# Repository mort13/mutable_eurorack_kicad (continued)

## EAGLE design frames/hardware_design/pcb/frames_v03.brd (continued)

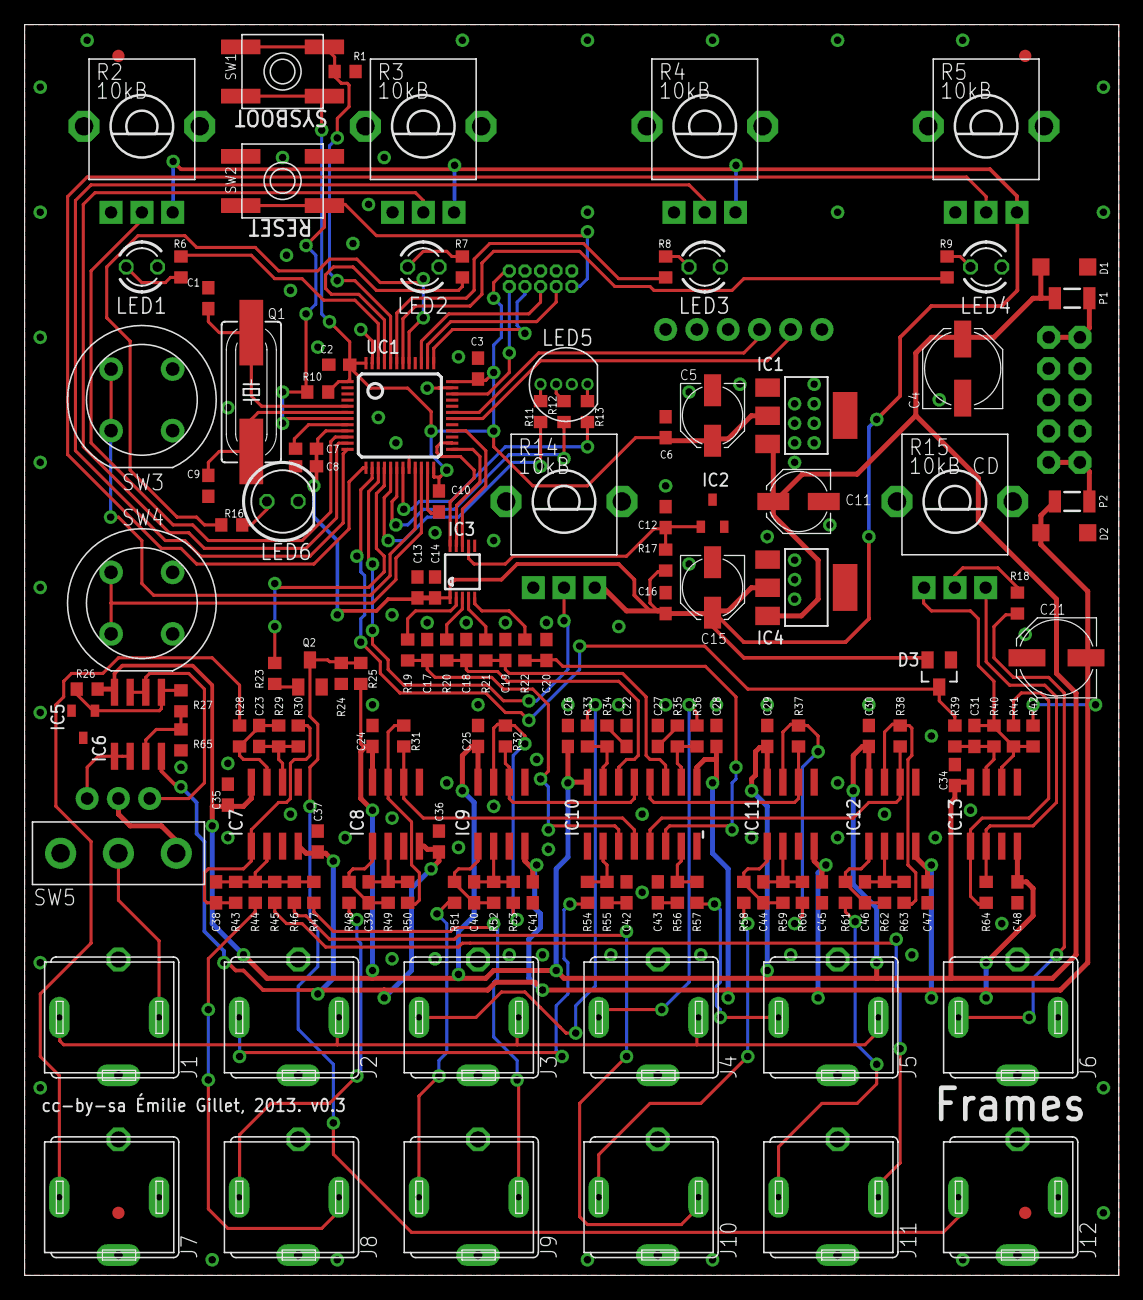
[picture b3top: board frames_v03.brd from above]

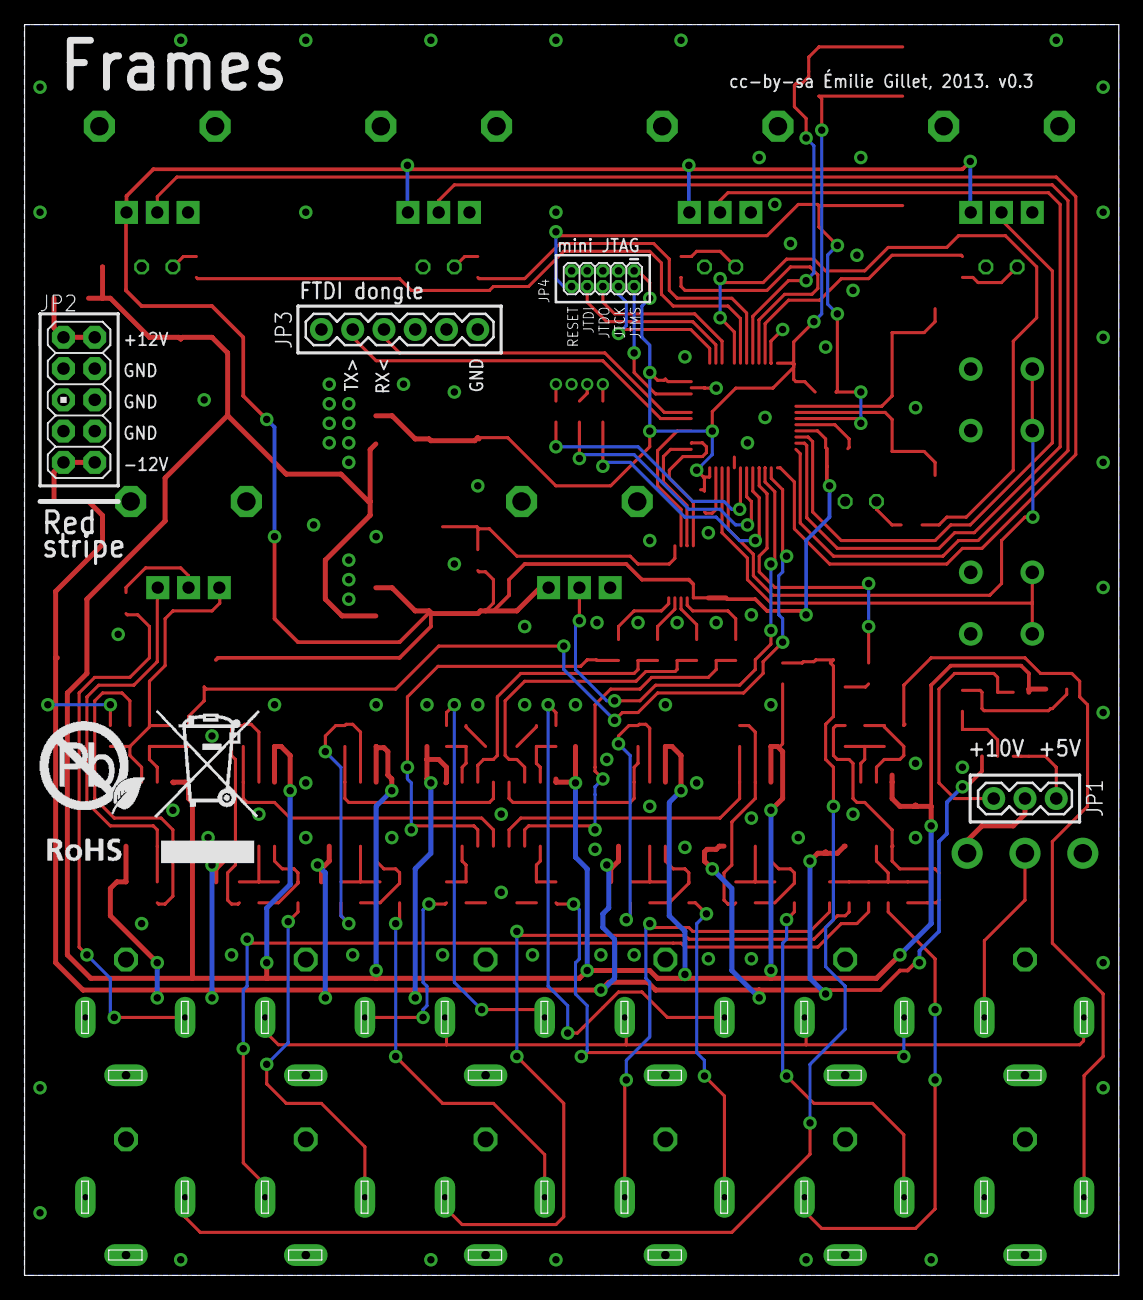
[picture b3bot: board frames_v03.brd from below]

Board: 2 copper layers, 88.9 x 101.6 mm, 165 parts (5 on the bottom side), 110 nets.

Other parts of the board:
U$1: EURORACK_TEMPLATE
U$3: ROHS_BIG

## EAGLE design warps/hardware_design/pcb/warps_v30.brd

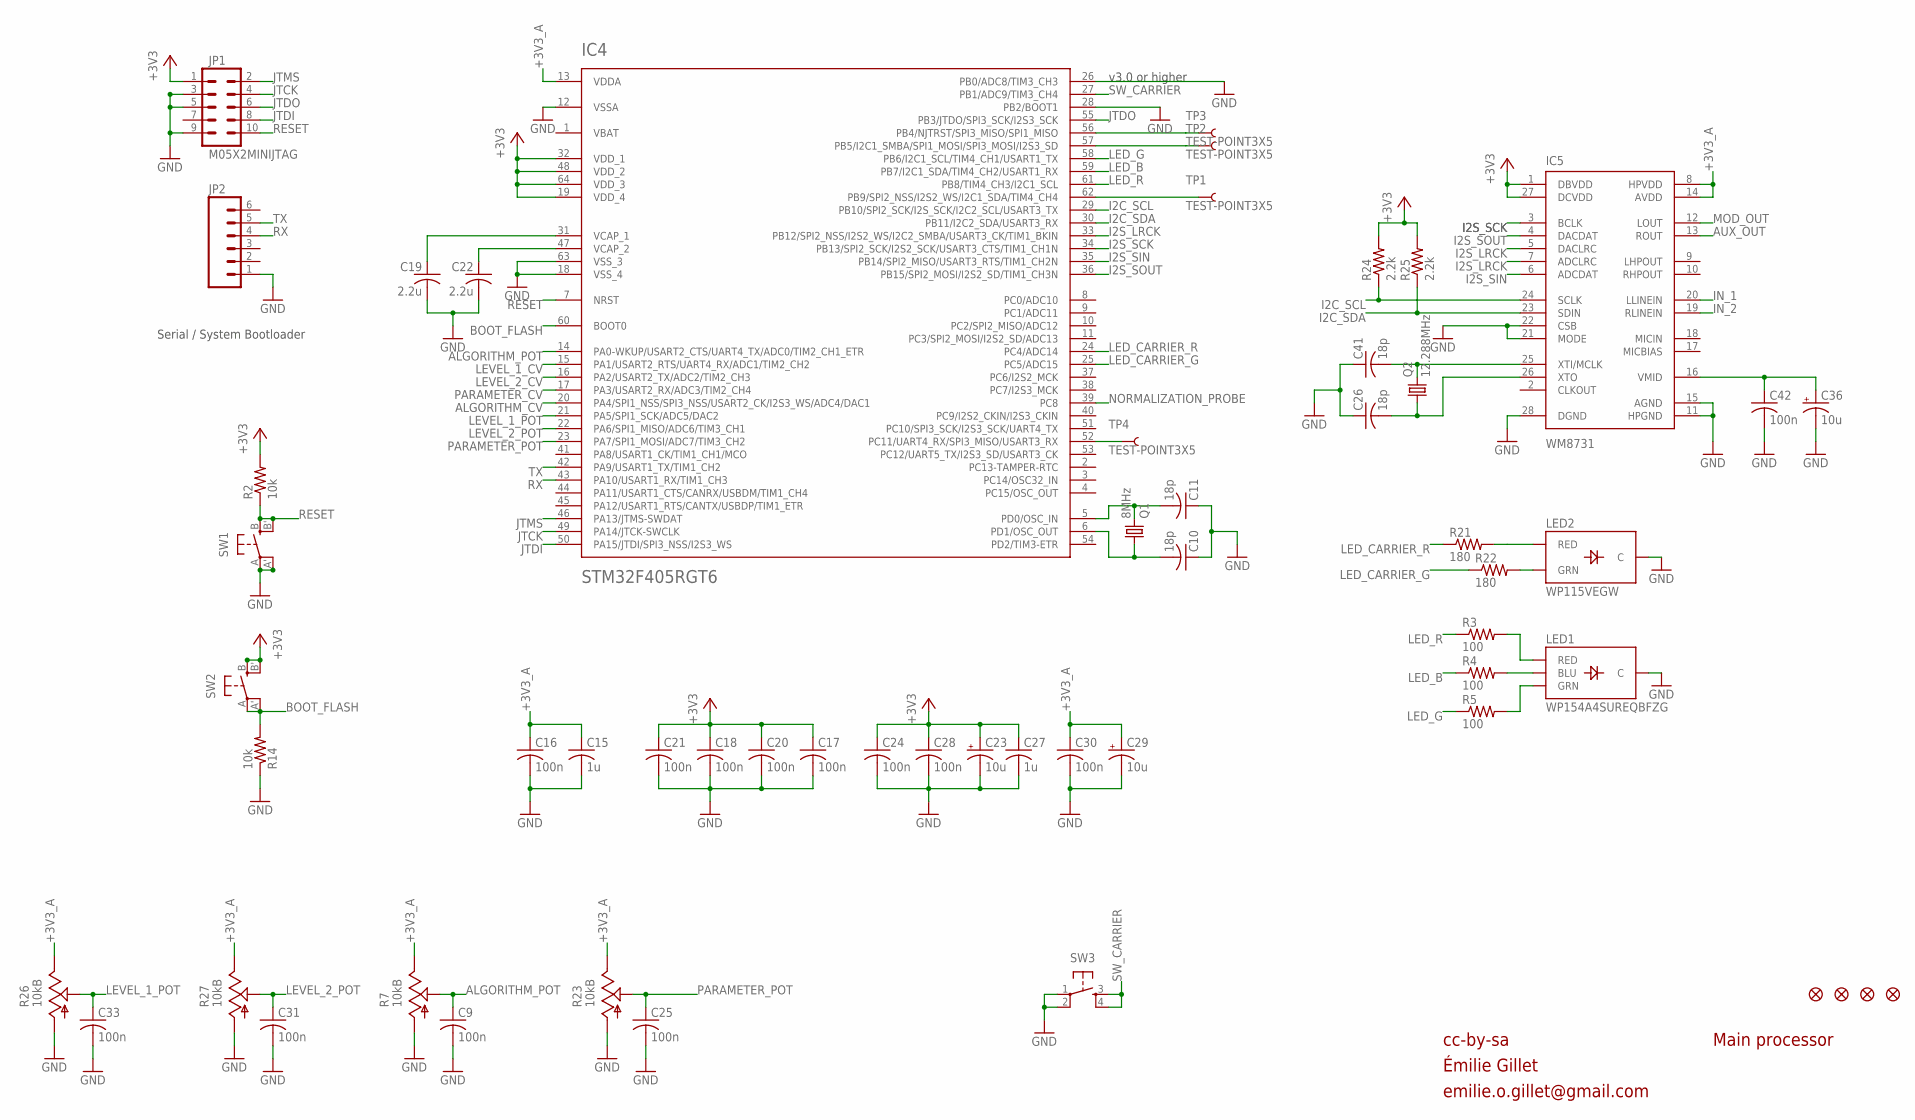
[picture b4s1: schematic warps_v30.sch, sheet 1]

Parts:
C9, C16, C17, C18, C20, C21, C24, C25, C28, C30, C31, C33, C42: 100n; C0603
C10, C11, C26, C41: 18p; C0603
C15, C27: 1u; C0603
C19, C22: 2.2u; C0805
C23, C29, C36: 10u; PANASONIC_A
F1, F2, F3, F4: FIDUCIAL1X2; FIDUCIAL-1X2
IC4: STM32F405RGT6; TQFP-10X10-64
IC5: WM8731; SSOP28
JP1: M05X2MINIJTAG; 2X5-1.27
JP2: M06SIP; 1X06
LED1: WP154A4SUREQBFZG; LED-TRICOLOR-THROUGHHOLE
LED2: WP115VEGW; LED-BICOLOR-THROUGHHOLE
Q1: 8MHz; HC49UP
Q2: 12.288MHz; HC49UP
R2, R14: 10k; R0603
R3, R4, R5: 100; R0603
R7, R23: 10kB; ALPS_POT_VERTICAL_PS
R21, R22: 180; R0603
R24, R25: 2.2k; R0603
R26, R27: 10kB; ALPS_POT_VERTICAL
SW1, SW2: EVQQ2; EVQ-Q2
SW3: TAC_SWITCHPTH; TACTILE-PTH
TP1, TP2, TP3, TP4: TEST-POINT3X5; PAD.03X.05

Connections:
+3V3: C17.1, C18.1, C20.1, C21.1, C23.+, C24.1, C27.1, C28.1, IC4.19 (VDD_4), IC4.32 (VDD_1), IC4.48 (VDD_2), IC4.64 (VDD_3), IC5.1 (DBVDD), IC5.27 (DCVDD), JP1.1, R2.2, R24.2, R25.2, SW2.B (S), SW2.B' (S1); also elsewhere on the board
+3V3_A: C15.1, C16.1, C29.+, C30.1, IC4.13 (VDDA), IC5.8 (HPVDD), IC5.14 (AVDD), R7.P$1 (E), R23.P$1 (E), R26.P$1 (E), R27.P$1 (E); also elsewhere on the board
ALGORITHM_CV: IC4.20 (PA4/SPI1_NSS/SPI3_NSS/USART2_CK/I2S3_WS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); also elsewhere on the board
ALGORITHM_POT: C9.1, IC4.14 (PA0-WKUP/USART2_CTS/UART4_TX/ADC0/TIM2_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), R7.P$2 (S)
AUX_OUT: IC5.13 (ROUT); also elsewhere on the board
BOOT_FLASH: IC4.60 (BOOT0), R14.2, SW2.A, SW2.A' (P1)
GND: C9.2, C10.1, C11.1, C15.2, C16.2, C17.2, C18.2, C19.2, C20.2, C21.2, C22.2, C23.-, C24.2, C25.2, C26.1, C27.2, C28.2, C29.-, C30.2, C31.2, C33.2, C36.-, C41.1, C42.2, IC4.12 (VSSA), IC4.18 (VSS_4), IC4.26 (PB0/ADC8/TIM3_CH3), IC4.28 (PB2/BOOT1), IC4.63 (VSS_3), IC5.11 (HPGND), IC5.15 (AGND), IC5.21 (MODE), IC5.22 (CSB), IC5.28 (DGND), JP1.3, JP1.5, JP1.9, JP2.1, LED1.GND (C), LED2.2 (C), R7.P$3 (A), R14.1, R23.P$3 (A), R26.P$3 (A), R27.P$3 (A), SW1.A, SW1.A' (P1), SW3.1, SW3.2; also elsewhere on the board
I2C_SCL: IC4.29 (PB10/SPI2_SCK/I2S_SCK/I2C2_SCL/USART3_TX), IC5.24 (SCLK), R24.1
I2C_SDA: IC4.30 (PB11/I2C2_SDA/USART3_RX), IC5.23 (SDIN), R25.1
I2S_LRCK: IC4.33 (PB12/SPI2_NSS/I2S2_WS/I2C2_SMBA/USART3_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), IC5.5 (DACLRC), IC5.7 (ADCLRC)
I2S_SCK: IC4.34 (PB13/SPI2_SCK/I2S2_SCK/USART3_CTS/TIM1_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), IC5.3 (BCLK)
I2S_SIN: IC4.35 (PB14/SPI2_MISO/USART3_RTS/TIM1_CH2N), IC5.6 (ADCDAT)
I2S_SOUT: IC4.36 (PB15/SPI2_MOSI/I2S2_SD/TIM1_CH3N), IC5.4 (DACDAT)
IN_1: IC5.20 (LLINEIN); also elsewhere on the board
IN_2: IC5.19 (RLINEIN); also elsewhere on the board
JTCK: IC4.49 (PA14/JTCK-SWCLK), JP1.4
JTDI: IC4.50 (PA15/JTDI/SPI3_NSS/I2S3_WS), JP1.8
JTDO: IC4.55 (PB3/JTDO/SPI3_SCK/I2S3_SCK), JP1.6
JTMS: IC4.46 (PA13/JTMS-SWDAT), JP1.2
LED_B: IC4.59 (PB7/I2C1_SDA/TIM4_CH2/USART1_RX), R4.1
LED_CARRIER_G: IC4.25 (PC5/ADC15), R22.1
LED_CARRIER_R: IC4.24 (PC4/ADC14), R21.1
LED_G: IC4.58 (PB6/I2C1_SCL/TIM4_CH1/USART1_TX), R5.1
LED_R: IC4.61 (PB8/TIM4_CH3/I2C1_SCL), R3.1
LEVEL_1_CV: IC4.15 (PA1/USART2_RTS/UART4_RX/ADC1/TIM2_CH2); also elsewhere on the board
LEVEL_1_POT: C33.1, IC4.21 (PA5/SPI1_SCK/ADC5/DAC2), R26.P$2 (S)
LEVEL_2_CV: IC4.16 (PA2/USART2_TX/ADC2/TIM2_CH3); also elsewhere on the board
LEVEL_2_POT: C31.1, IC4.22 (PA6/SPI1_MISO/ADC6/TIM3_CH1), R27.P$2 (S)
MOD_OUT: IC5.12 (LOUT); also elsewhere on the board
unnamed: LED2.3 (RED), R21.2
unnamed: C11.2, IC4.5 (PD0/OSC_IN), Q1.2
unnamed: C10.2, IC4.6 (PD1/OSC_OUT), Q1.1
unnamed: C22.1, IC4.47 (VCAP_2)
unnamed: LED2.1 (GRN), R22.2
unnamed: C36.+, C42.1, IC5.16 (VMID)
unnamed: C19.1, IC4.31 (VCAP_1)
unnamed: IC4.56 (PB4/NJTRST/SPI3_MISO/SPI1_MISO), TP3.P$1
unnamed: IC4.57 (PB5/I2C1_SMBA/SPI1_MOSI/SPI3_MOSI/I2S3_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), TP2.P$1
unnamed: IC4.52 (PC11/UART4_RX/SPI3_MISO/USART3_RX), TP4.P$1
unnamed: IC4.62 (PB9/SPI2_NSS/I2S2_WS/I2C1_SDA/TIM4_CH4), TP1.P$1
unnamed: LED1.RED, R3.2
unnamed: LED1.BLU, R4.2
unnamed: LED1.GRN, R5.2
unnamed: C41.2, IC5.25 (XTI/MCLK), Q2.2
unnamed: C26.2, IC5.26 (XTO), Q2.1
NORMALIZATION_PROBE: IC4.39 (PC8); also elsewhere on the board
PARAMETER_CV: IC4.17 (PA3/USART2_RX/ADC3/TIM2_CH4); also elsewhere on the board
PARAMETER_POT: C25.1, IC4.23 (PA7/SPI1_MOSI/ADC7/TIM3_CH2), R23.P$2 (S)
RESET: IC4.7 (NRST), JP1.10, R2.1, SW1.B (S), SW1.B' (S1)
RX: IC4.43 (PA10/USART1_RX/TIM1_CH3), JP2.4
SW_CARRIER: IC4.27 (PB1/ADC9/TIM3_CH4), SW3.3, SW3.4
TX: IC4.42 (PA9/USART1_TX/TIM1_CH2), JP2.5
VBAT: IC4.1 (VBAT)

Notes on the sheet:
cc-by-sa
Main processor
Serial / System Bootloader
v3.0 or higher
Émilie Gillet
emilie.o.gillet@gmail.com

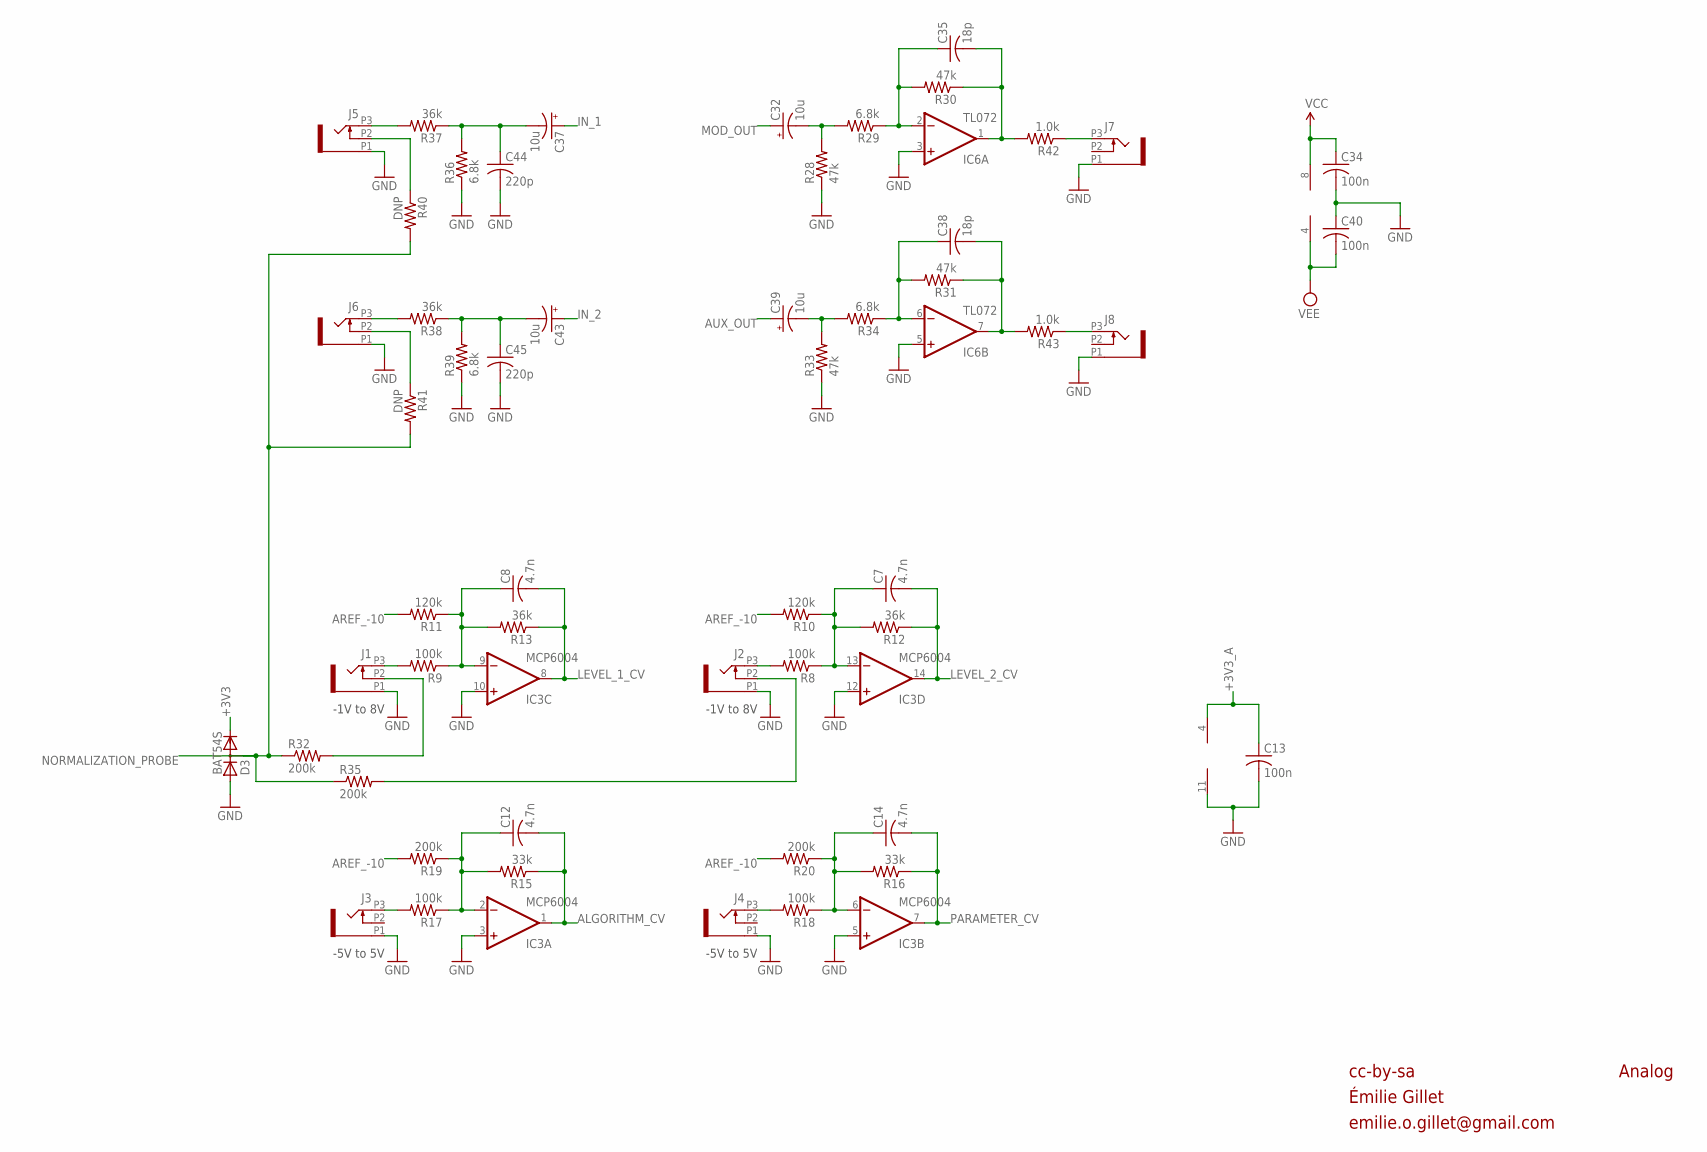
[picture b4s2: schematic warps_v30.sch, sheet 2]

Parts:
C7, C8, C12, C14: 4.7n; C0603
C13, C34, C40: 100n; C0603
C32, C37, C39, C43: 10u; PANASONIC_A
C35, C38: 18p; C0603
C44, C45: 220p; C0603
D3: BAT54S; SOT23
IC3: MCP6004; SO14
IC6: TL072; SO08
J1, J2, J3, J4, J5, J6, J7, J8: PJ301_THONKICONN6; WQP_PJ_301M6
R8, R9, R17, R18: 100k; R0603
R10, R11: 120k; R0603
R12, R13, R37, R38: 36k; R0603
R15, R16: 33k; R0603
R19, R20, R32, R35: 200k; R0603
R28, R30, R31, R33: 47k; R0603
R29, R34, R36, R39: 6.8k; R0603
R40, R41: DNP; R0603
R42, R43: 1.0k; R0603

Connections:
+3V3: D3.2 (C); also elsewhere on the board
+3V3_A: C13.1, IC3.4 (V+); also elsewhere on the board
ALGORITHM_CV: C12.2, IC3.1 (OUT), R15.1; also elsewhere on the board
AREF_-10: R10.2, R11.2, R19.2, R20.2; also elsewhere on the board
AUX_OUT: C39.+; also elsewhere on the board
GND: C13.2, C34.2, C40.1, C44.2, C45.2, D3.1 (A), IC3.3 (+IN), IC3.5 (+IN), IC3.10 (+IN), IC3.11 (V-), IC3.12 (+IN), IC6.3 (+IN), IC6.5 (+IN), J1.P1 (1), J2.P1 (1), J3.P1 (1), J4.P1 (1), J5.P1 (1), J6.P1 (1), J7.P1 (1), J8.P1 (1), R28.1, R33.1, R36.1, R39.1; also elsewhere on the board
IN_1: C37.+; also elsewhere on the board
IN_2: C43.+; also elsewhere on the board
LEVEL_1_CV: C8.2, IC3.8 (OUT), R13.1; also elsewhere on the board
LEVEL_2_CV: C7.2, IC3.14 (OUT), R12.1; also elsewhere on the board
MOD_OUT: C32.+; also elsewhere on the board
unnamed: J1.P3 (3), R9.2
unnamed: C8.1, IC3.9 (-IN), R9.1, R11.1, R13.2
unnamed: J2.P3 (3), R8.2
unnamed: C7.1, IC3.13 (-IN), R8.1, R10.1, R12.2
unnamed: J4.P3 (3), R18.2
unnamed: J1.P2 (2), R32.2
unnamed: J3.P3 (3), R17.2
unnamed: C12.1, IC3.2 (-IN), R15.2, R17.1, R19.1
unnamed: J2.P2 (2), R35.2
unnamed: C14.1, IC3.6 (-IN), R16.2, R18.1, R20.1
unnamed: C37.-, C44.1, R36.2, R37.1
unnamed: J6.P3 (3), R38.2
unnamed: J5.P3 (3), R37.2
unnamed: C43.-, C45.1, R38.1, R39.2
unnamed: C39.-, R33.2, R34.2
unnamed: C38.1, IC6.6 (-IN), R31.2, R34.1
unnamed: C38.2, IC6.7 (OUT), R31.1, R43.2
unnamed: J8.P3 (3), R43.1
unnamed: C32.-, R28.2, R29.2
unnamed: C35.1, IC6.2 (-IN), R29.1, R30.2
unnamed: C35.2, IC6.1 (OUT), R30.1, R42.2
unnamed: J7.P3 (3), R42.1
unnamed: J6.P2 (2), R41.1
unnamed: J5.P2 (2), R40.1
NORMALIZATION_PROBE: D3.3 (AC), R32.1, R35.1, R40.2, R41.2; also elsewhere on the board
PARAMETER_CV: C14.2, IC3.7 (OUT), R16.1; also elsewhere on the board
VCC: C34.1, IC6.8 (V+); also elsewhere on the board
VEE: C40.2, IC6.4 (V-); also elsewhere on the board

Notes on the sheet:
cc-by-sa
Analog
-1V to 8V
-5V to 5V
Émilie Gillet
emilie.o.gillet@gmail.com

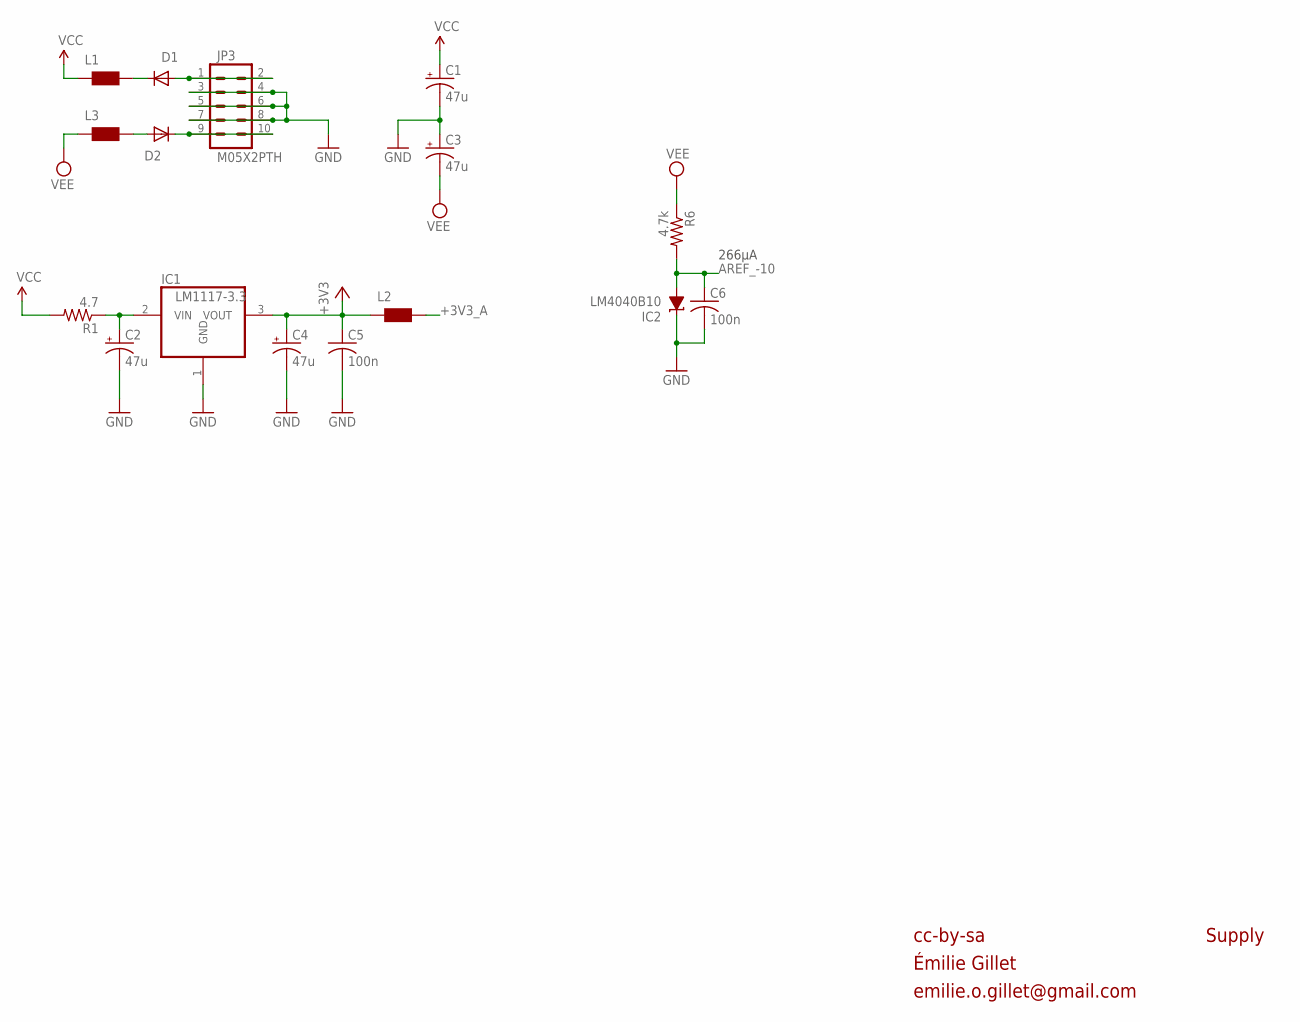
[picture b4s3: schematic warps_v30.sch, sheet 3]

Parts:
C1, C2, C3, C4: 47u; PANASONIC_D
C5, C6: 100n; C0603
D1, D2: 1N5819HW; SOD123
IC1: LM1117-3.3; TO252
IC2: LM4040B10; DBZ_R-PDSO-G3
JP3: M05X2PTH; AVR_ICSP
L1, L2, L3: WE-CBF_0603; 0603
R1: 4.7; R1206
R6: 4.7k; R0603

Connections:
+3V3: C4.+, C5.1, IC1.3 (VOUT), L2.1; also elsewhere on the board
+3V3_A: L2.2; also elsewhere on the board
AREF_-10: C6.1, IC2.2 (A), R6.2; also elsewhere on the board
GND: C1.-, C2.-, C3.+, C4.-, C5.2, C6.2, IC1.1 (GND), IC2.1 (C), JP3.3, JP3.4, JP3.5, JP3.6, JP3.7, JP3.8; also elsewhere on the board
unnamed: C2.+, IC1.2 (VIN), R1.1
unnamed: D1.C, L1.2
unnamed: D2.A, L3.2
unnamed: D1.A, JP3.1, JP3.2
unnamed: D2.C, JP3.9, JP3.10
VCC: C1.+, L1.1, R1.2; also elsewhere on the board
VEE: C3.-, L3.1, R6.1; also elsewhere on the board

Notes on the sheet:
266µA
cc-by-sa
Supply
Émilie Gillet
emilie.o.gillet@gmail.com

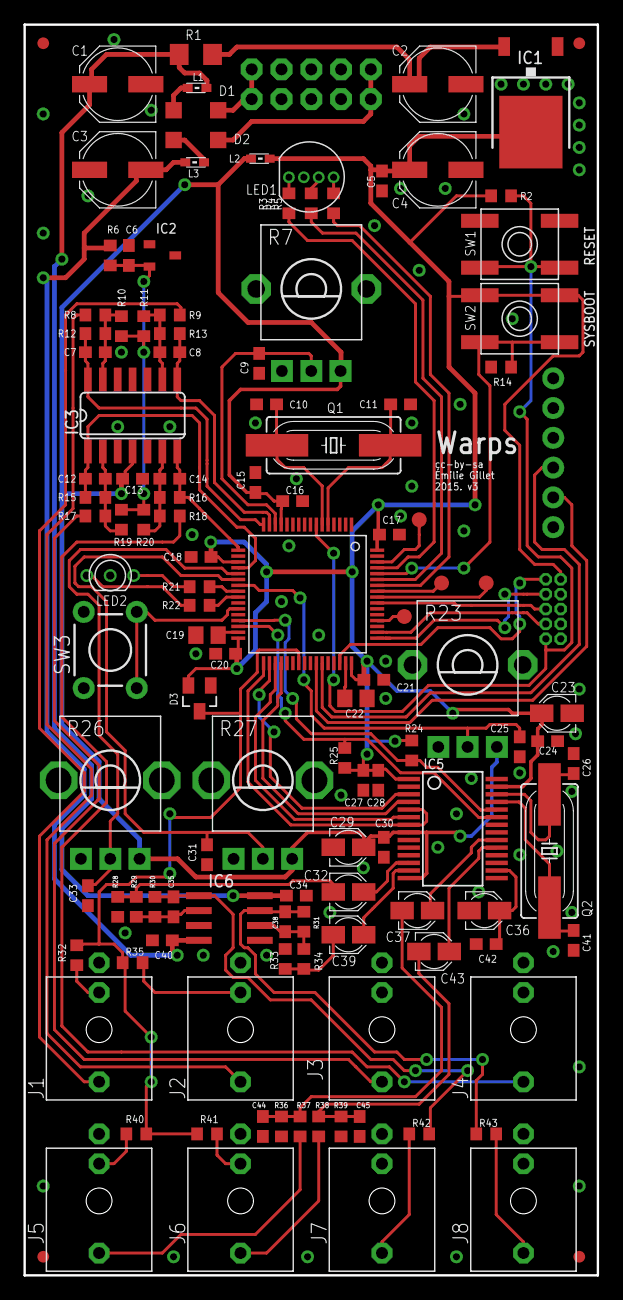
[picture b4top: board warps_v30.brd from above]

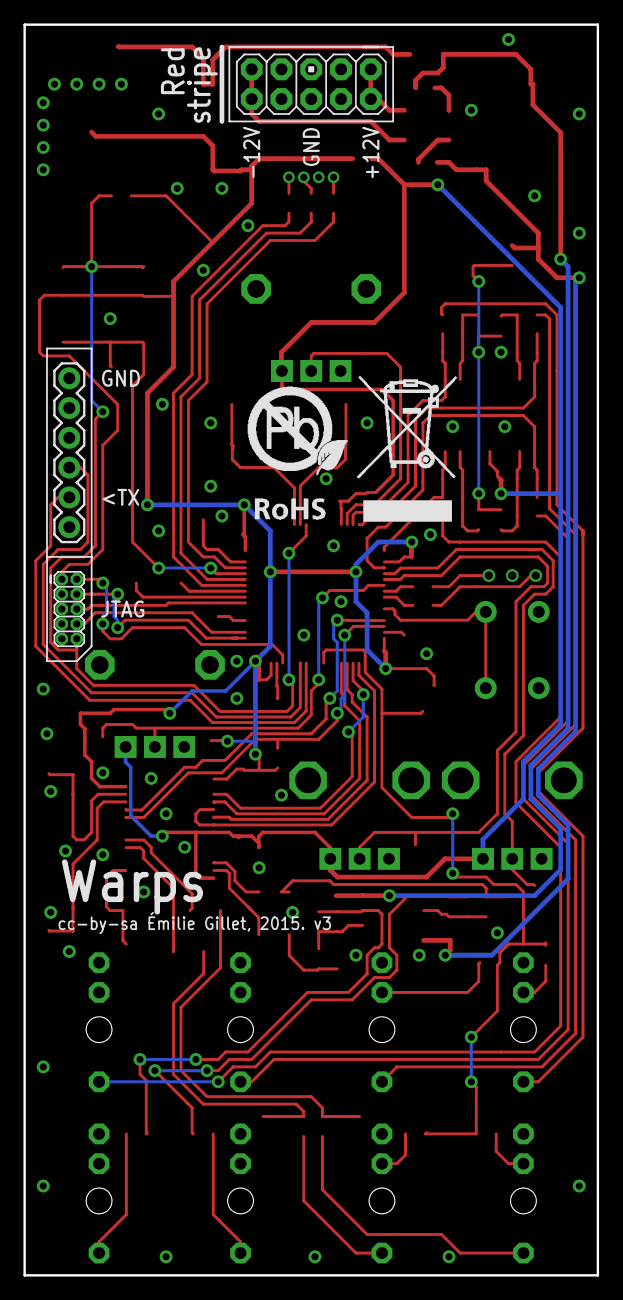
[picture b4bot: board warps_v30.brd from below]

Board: 2 copper layers, 48.9 x 106.7 mm, 127 parts (4 on the bottom side), 84 nets.

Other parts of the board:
U$2: ROHS_BIG

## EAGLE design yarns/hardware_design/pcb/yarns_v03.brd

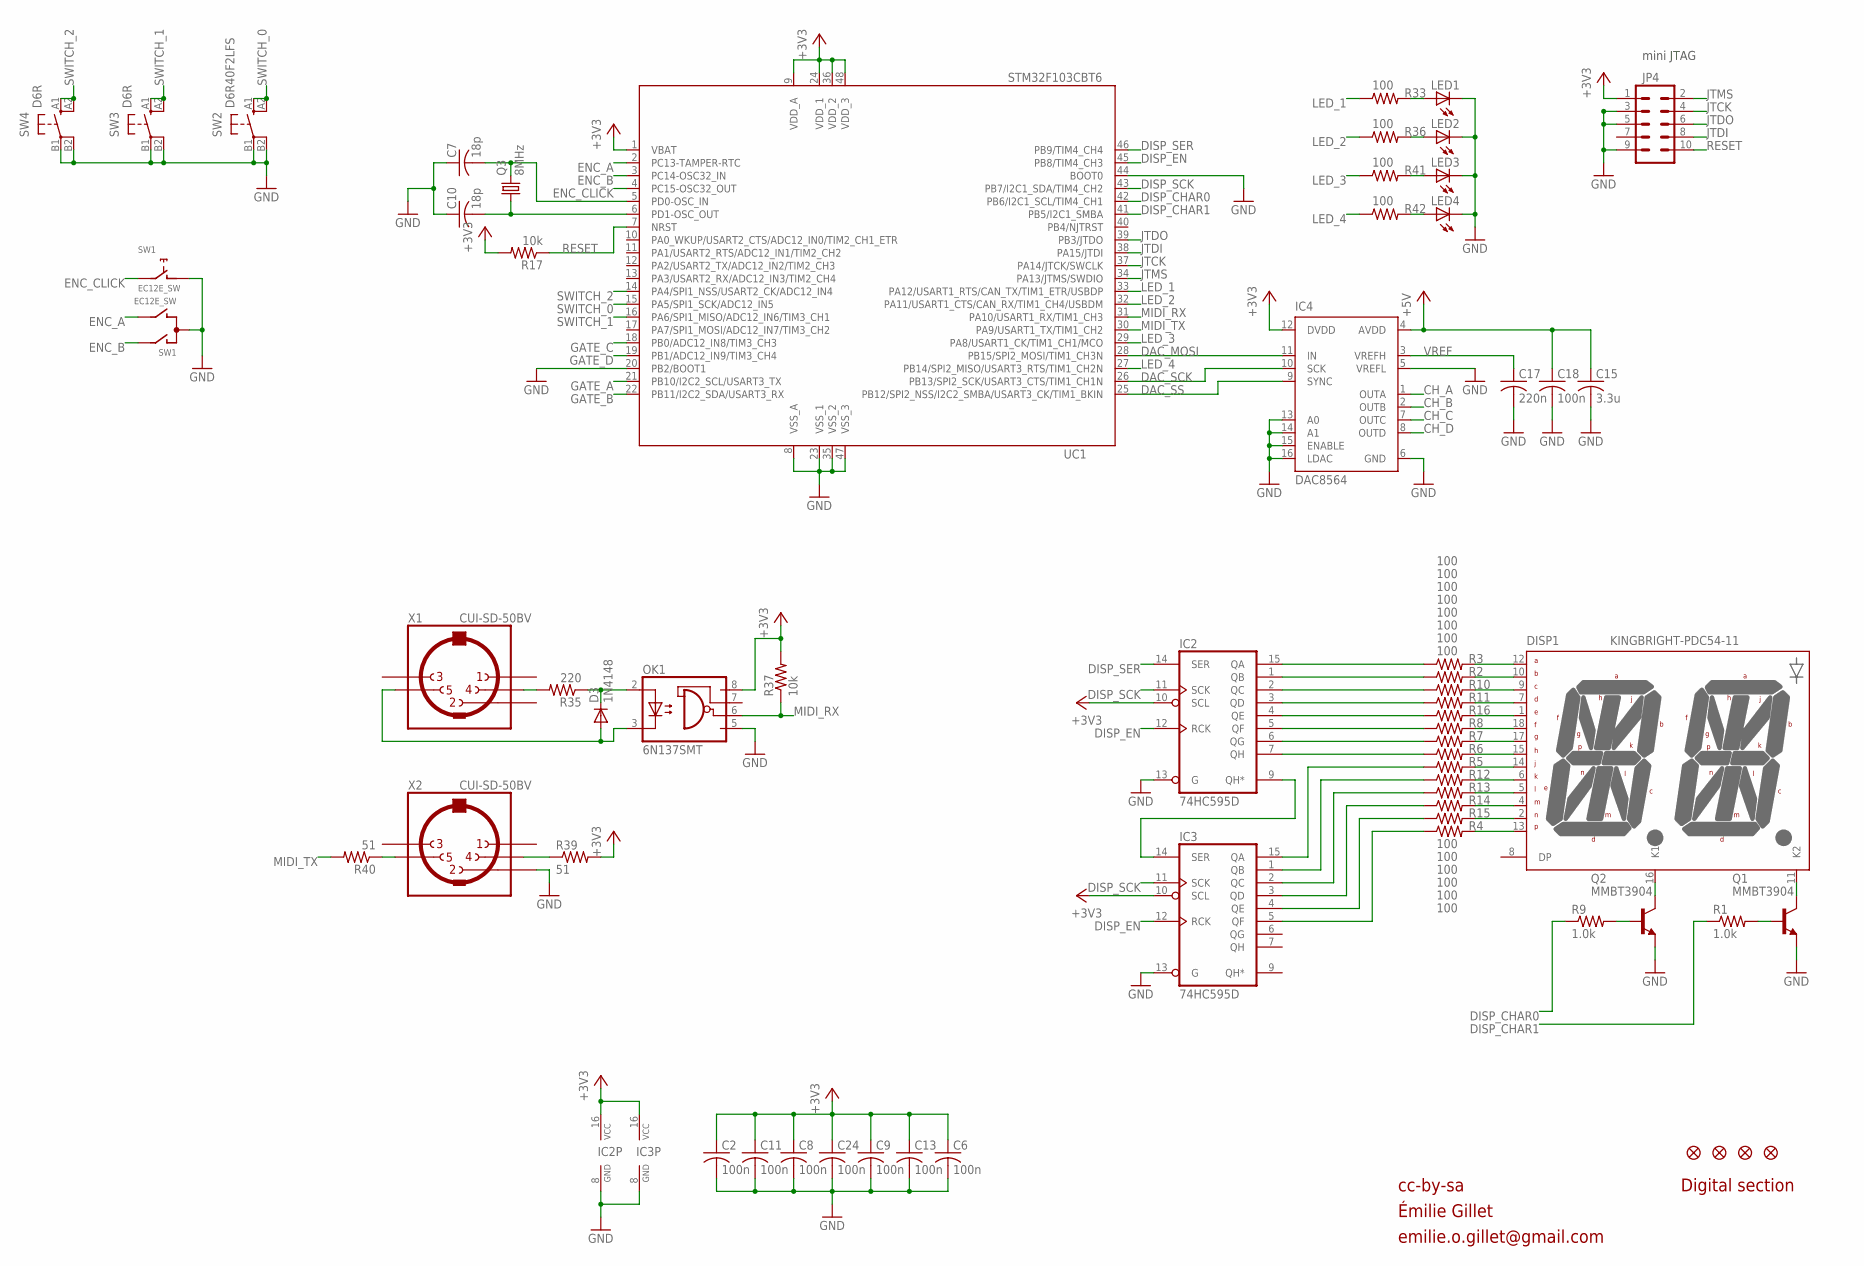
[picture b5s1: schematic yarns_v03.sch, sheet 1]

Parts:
C2, C6, C8, C9, C11, C13, C18, C24: 100n; C0603
C7, C10: 18p; C0603
C15: 3.3u; C0603
C17: 220n; C0603
D3: 1N4148; SOD323-W
DISP1: KINGBRIGHT-PDC54-11; PDC54
F1, F3, F5, F6: FIDUCIAL1X2; FIDUCIAL-1X2
IC2, IC3: 74HC595D; SO16
IC4: DAC8564; SOP65P640X110-16N
JP4: M05X2MINIJTAG; 2X5-1.27
LED1, LED2, LED3, LED4: LED3MM
OK1: 6N137SMT; DIL8-SMD
Q1, Q2: MMBT3904; SOT23-BEC
Q3: 8MHz; HC49UP
R1, R9: 1.0k; R0603
R2, R3, R4, R5, R6, R7, R8, R10, R11, R12, R13, R14, R15, R16, R33, R36, R41, R42: 100; R0603
R17, R37: 10k; R0603
R35: 220; R0603
R39, R40: 51; R0603
SW1: EC12E_SW; ALPS_EC12E_SW
SW2: D6R40F2LFS; D6R
SW3, SW4: D6R
UC1: STM32F103CBT6; LQFP48
X1, X2: CUI-SD-50BV; SD-50BV

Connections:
+3V3: C2.1, C6.1, C8.1, C9.1, C11.1, C13.1, C24.1, IC2.10 (SCL), IC2.16 (VCC), IC3.10 (SCL), IC3.16 (VCC), IC4.12 (DVDD), JP4.1, OK1.8 (VCC), R17.2, R37.2, R39.2, UC1.1 (VBAT), UC1.9 (VDD_A), UC1.24 (VDD_1), UC1.36 (VDD_2), UC1.48 (VDD_3); also elsewhere on the board
+5V: C15.1, C18.1, IC4.4 (AVDD); also elsewhere on the board
CH_A: IC4.1 (OUTA); also elsewhere on the board
CH_B: IC4.2 (OUTB); also elsewhere on the board
CH_C: IC4.7 (OUTC); also elsewhere on the board
CH_D: IC4.8 (OUTD); also elsewhere on the board
DAC_MOSI: IC4.11 (IN), UC1.28 (PB15/SPI2_MOSI/TIM1_CH3N)
DAC_SCK: IC4.10 (SCK), UC1.26 (PB13/SPI2_SCK/USART3_CTS/TIM1_CH1N)
DAC_SS: IC4.9 (SYNC), UC1.25 (PB12/SPI2_NSS/I2C2_SMBA/USART3_CK/TIM1_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)
DISP_CHAR0: R9.1, UC1.42 (PB6/I2C1_SCL/TIM4_CH1)
DISP_CHAR1: R1.1, UC1.41 (PB5/I2C1_SMBA)
DISP_EN: IC2.12 (RCK), IC3.12 (RCK), UC1.45 (PB8/TIM4_CH3)
DISP_SCK: IC2.11 (SCK), IC3.11 (SCK), UC1.43 (PB7/I2C1_SDA/TIM4_CH2)
DISP_SER: IC2.14 (SER), UC1.46 (PB9/TIM4_CH4)
ENC_A: SW1.B, UC1.2 (PC13-TAMPER-RTC)
ENC_B: SW1.A, UC1.3 (PC14-OSC32_IN)
ENC_CLICK: SW1.E (2), UC1.4 (PC15-OSC32_OUT)
GATE_A: UC1.21 (PB10/I2C2_SCL/USART3_TX); also elsewhere on the board
GATE_B: UC1.22 (PB11/I2C2_SDA/USART3_RX); also elsewhere on the board
GATE_C: UC1.18 (PB0/ADC12_IN8/TIM3_CH3); also elsewhere on the board
GATE_D: UC1.19 (PB1/ADC12_IN9/TIM3_CH4); also elsewhere on the board
GND: C2.2, C6.2, C7.1, C8.2, C9.2, C10.1, C11.2, C13.2, C15.2, C17.2, C18.2, C24.2, IC2.8 (GND), IC2.13 (G), IC3.8 (GND), IC3.13 (G), IC4.5 (VREFL), IC4.6 (GND), IC4.13 (A0), IC4.14 (A1), IC4.15 (ENABLE), IC4.16 (LDAC), JP4.3, JP4.5, JP4.9, LED1.K (C), LED2.K (C), LED3.K (C), LED4.K (C), OK1.5 (GND), Q1.E, Q2.E, SW1.C, SW1.D (1), SW2.B1, SW2.B2 (P1), SW3.B1, SW3.B2 (P1), SW4.B1, SW4.B2 (P1), UC1.8 (VSS_A), UC1.20 (PB2/BOOT1), UC1.23 (VSS_1), UC1.35 (VSS_2), UC1.44 (BOOT0), UC1.47 (VSS_3), X2.2; also elsewhere on the board
JTCK: JP4.4, UC1.37 (PA14/JTCK/SWCLK)
JTDI: JP4.8, UC1.38 (PA15/JTDI)
JTDO: JP4.6, UC1.39 (PB3/JTDO)
JTMS: JP4.2, UC1.34 (PA13/JTMS/SWDIO)
LED_1: R33.1, UC1.33 (PA12/USART1_RTS/CAN_TX/TIM1_ETR/USBDP)
LED_2: R36.1, UC1.32 (PA11/USART1_CTS/CAN_RX/TIM1_CH4/USBDM)
LED_3: R41.1, UC1.29 (PA8/USART1_CK/TIM1_CH1/MCO)
LED_4: R42.1, UC1.27 (PB14/SPI2_MISO/USART3_RTS/TIM1_CH2N)
MIDI_RX: OK1.6 (VO), R37.1, UC1.31 (PA10/USART1_RX/TIM1_CH3)
MIDI_TX: R40.2, UC1.30 (PA9/USART1_TX/TIM1_CH2)
unnamed: DISP1.16 (K1), Q2.C
unnamed: DISP1.11 (K2), Q1.C
unnamed: C7.2, Q3.2, UC1.5 (PD0-OSC_IN)
unnamed: C10.2, Q3.1, UC1.6 (PD1-OSC_OUT)
unnamed: Q2.B, R9.2
unnamed: Q1.B, R1.2
unnamed: D3.C, OK1.2 (A), R35.1
unnamed: R35.2, X1.4
unnamed: R40.1, X2.5
unnamed: DISP1.17 (G), R7.2
unnamed: D3.A, OK1.3 (C), X1.5
unnamed: R39.1, X2.4
unnamed: DISP1.12 (A), R3.2
unnamed: DISP1.10 (B), R2.2
unnamed: DISP1.9 (C), R10.2
unnamed: DISP1.7 (D), R11.2
unnamed: DISP1.1 (E), R16.2
unnamed: DISP1.18 (F), R8.2
unnamed: DISP1.15 (H), R6.2
unnamed: DISP1.14 (J), R5.2
unnamed: DISP1.6 (K), R12.2
unnamed: DISP1.5 (L), R13.2
unnamed: DISP1.4 (M), R14.2
unnamed: DISP1.2 (N), R15.2
unnamed: DISP1.13, R4.2
unnamed: IC2.7 (QH), R6.1
unnamed: IC2.9 (QH*), IC3.14 (SER)
unnamed: IC2.15 (QA), R3.1
unnamed: IC2.1 (QB), R2.1
unnamed: IC2.2 (QC), R10.1
unnamed: IC2.3 (QD), R11.1
unnamed: IC2.4 (QE), R16.1
unnamed: IC2.5 (QF), R8.1
unnamed: IC2.6 (QG), R7.1
unnamed: IC3.15 (QA), R5.1
unnamed: IC3.1 (QB), R12.1
unnamed: IC3.2 (QC), R13.1
unnamed: IC3.3 (QD), R14.1
unnamed: IC3.4 (QE), R15.1
unnamed: IC3.5 (QF), R4.1
unnamed: LED1.A, R33.2
unnamed: LED2.A, R36.2
unnamed: LED3.A, R41.2
unnamed: LED4.A, R42.2
RESET: JP4.10, R17.1, UC1.7 (NRST)
SWITCH_0: SW2.A1 (S), SW2.A2 (S1), UC1.15 (PA5/SPI1_SCK/ADC12_IN5)
SWITCH_1: SW3.A1 (S), SW3.A2 (S1), UC1.16 (PA6/SPI1_MISO/ADC12_IN6/TIM3_CH1)
SWITCH_2: SW4.A1 (S), SW4.A2 (S1), UC1.14 (PA4/SPI1_NSS/USART2_CK/ADC12_IN4)
VREF: C17.1, IC4.3 (VREFH); also elsewhere on the board

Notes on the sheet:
cc-by-sa
Digital section
mini JTAG
Émilie Gillet
emilie.o.gillet@gmail.com
